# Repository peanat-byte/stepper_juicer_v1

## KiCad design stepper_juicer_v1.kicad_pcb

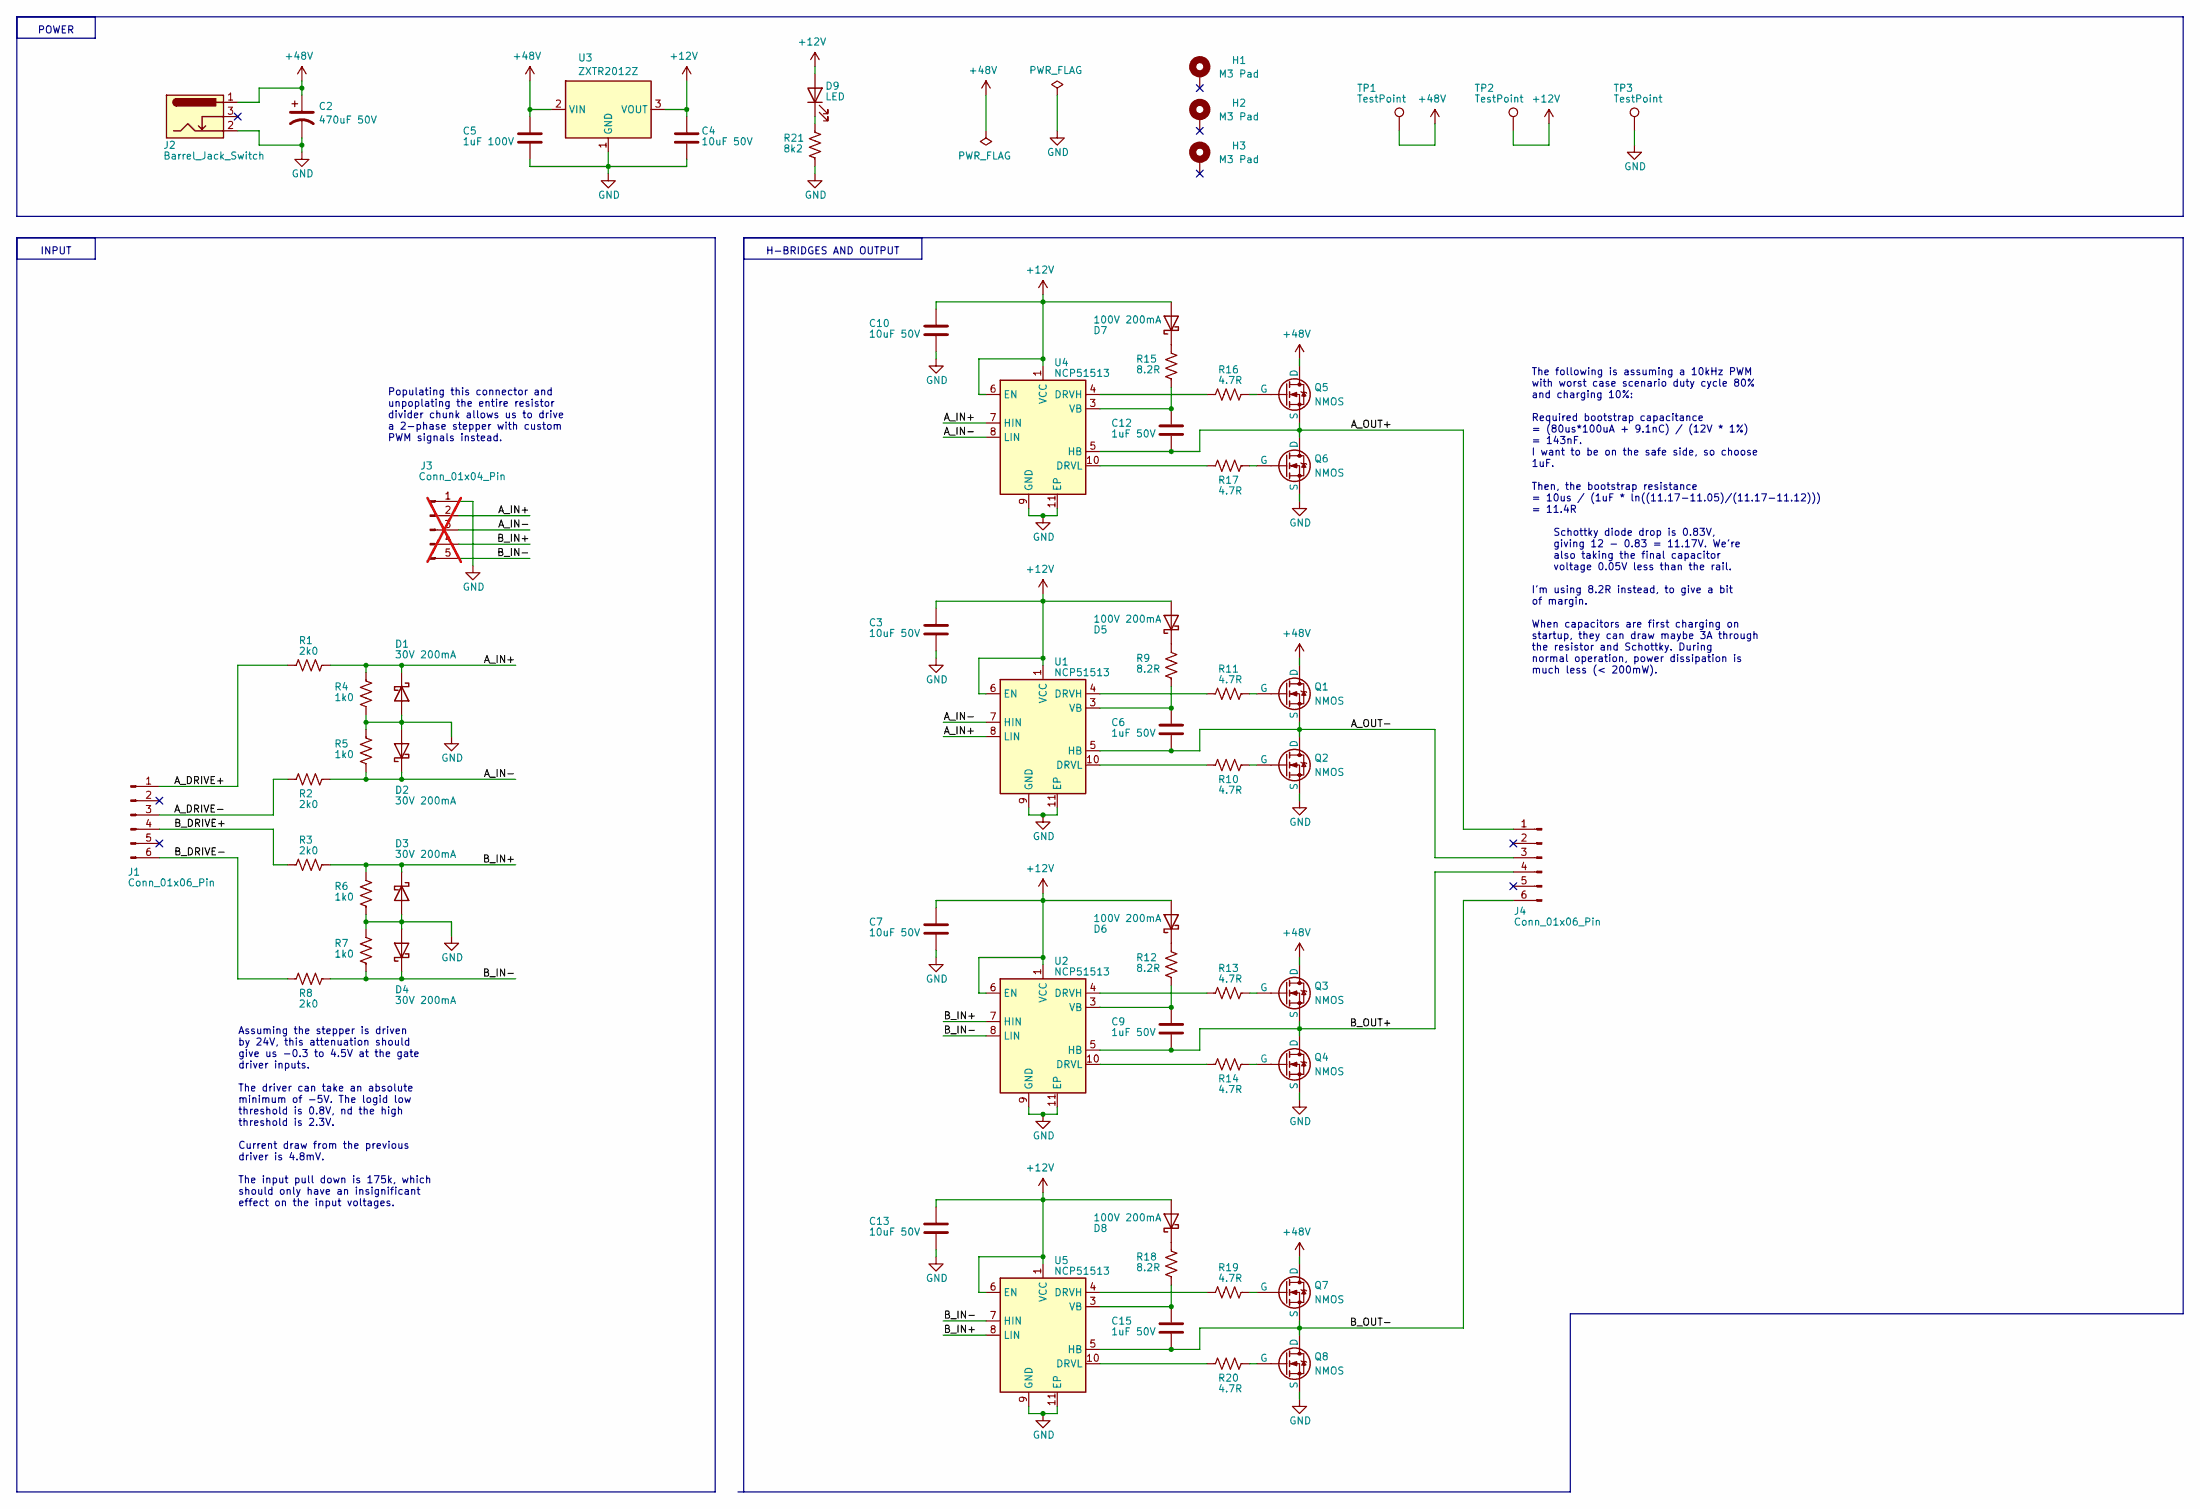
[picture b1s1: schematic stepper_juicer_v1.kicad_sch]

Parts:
C2: 470uF 50V; CP_Radial_D10.0mm_P5.00mm
C3, C4, C7, C10, C13: 10uF 50V; C_0805_2012Metric
C5: 1uF 100V; C_0805_2012Metric
C6, C9, C12, C15: 1uF 50V; C_0805_2012Metric
D1, D2, D3, D4: 30V 200mA; D_SOD-523
D5, D6, D7, D8: 100V 200mA; D_SOD-323F
D9: LED; D_0603_1608Metric
H1, H2, H3: M3 Pad; MountingHole_3.2mm_M3_Pad
J1, J4: Conn_01x06_Pin; JST_PH_B6B-PH-K_1x06_P2.00mm_Vertical
J2: Barrel_Jack_Switch; BarrelJack_GCT_DCJ200-10-A_Horizontal
J3: Conn_01x04_Pin; JST_XH_B5B-XH-A_1x05_P2.50mm_Vertical; not fitted
Q1, Q2, Q3, Q4, Q5, Q6, Q7, Q8: NMOS; PG-TSDSON-8_3.8x2.29_Pitch0.65mm
R1, R2, R3, R8: 2k0; R_0603_1608Metric
R4, R5, R6, R7: 1k0; R_0603_1608Metric
R9, R12, R15, R18: 8.2R; R_0603_1608Metric
R10, R11, R13, R14, R16, R17, R19, R20: 4.7R; R_0805_2012Metric
R21: 8k2; R_0603_1608Metric
TP1, TP2, TP3: TestPoint; TestPoint_Pad_D1.0mm
U1, U2, U4, U5: NCP51513; DFN-10-1EP_3x3mm_P0.5mm_EP1.7x2.5mm
U3: ZXTR2012Z; SOT-89-3

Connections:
+12V: C3.1, C4.1, C7.1, C10.1, C13.1, D5.2 (A), D6.2 (A), D7.2 (A), D8.2 (A), D9.2 (A), TP2.1, U1.1 (VCC), U1.6 (EN), U2.1 (VCC), U2.6 (EN), U3.3 (VOUT), U4.1 (VCC), U4.6 (EN), U5.1 (VCC), U5.6 (EN)
+48V: C2.1, C5.1, J2.1, Q1.1 (D), Q3.1 (D), Q5.1 (D), Q7.1 (D), TP1.1, U3.2 (VIN)
/A_DRIVE+: J1.1, R1.2
/A_DRIVE-: J1.3, R2.2
/A_IN+: D1.1 (K), J3.2, R1.1, R4.1, U1.8 (LIN), U4.7 (HIN)
/A_IN-: D2.1 (K), J3.3, R2.1, R5.2, U1.7 (HIN), U4.8 (LIN)
/A_OUT+: C12.2, J4.1, Q5.3 (S), Q6.1 (D), U4.5 (HB)
/A_OUT-: C6.2, J4.3, Q1.3 (S), Q2.1 (D), U1.5 (HB)
/B_DRIVE+: J1.4, R3.2
/B_DRIVE-: J1.6, R8.2
/B_IN+: D3.1 (K), J3.4, R3.1, R6.1, U2.7 (HIN), U5.8 (LIN)
/B_IN-: D4.1 (K), J3.5, R7.2, R8.1, U2.8 (LIN), U5.7 (HIN)
/B_OUT+: C9.2, J4.4, Q3.3 (S), Q4.1 (D), U2.5 (HB)
/B_OUT-: C15.2, J4.6, Q7.3 (S), Q8.1 (D), U5.5 (HB)
GND: C2.2, C3.2, C4.2, C5.2, C7.2, C10.2, C13.2, D1.2 (A), D2.2 (A), D3.2 (A), D4.2 (A), J2.2, J3.1, Q2.3 (S), Q4.3 (S), Q6.3 (S), Q8.3 (S), R4.2, R5.1, R6.2, R7.1, R21.2, TP3.1, U1.9 (GND), U1.11 (EP), U2.9 (GND), U2.11 (EP), U3.1 (GND), U4.9 (GND), U4.11 (EP), U5.9 (GND), U5.11 (EP)
unnamed: D5.1 (K), R9.2
unnamed: D6.1 (K), R12.2
unnamed: D7.1 (K), R15.2
unnamed: D8.1 (K), R18.2
unnamed: D9.1 (K), R21.1
unnamed: Q1.2 (G), R11.1
unnamed: Q2.2 (G), R10.1
unnamed: Q3.2 (G), R13.1
unnamed: Q4.2 (G), R14.1
unnamed: Q5.2 (G), R16.1
unnamed: Q6.2 (G), R17.1
unnamed: Q7.2 (G), R19.1
unnamed: Q8.2 (G), R20.1
unnamed: R11.2, U1.4 (DRVH)
unnamed: R10.2, U1.10 (DRVL)
unnamed: C6.1, R9.1, U1.3 (VB)
unnamed: R13.2, U2.4 (DRVH)
unnamed: R14.2, U2.10 (DRVL)
unnamed: C9.1, R12.1, U2.3 (VB)
unnamed: R16.2, U4.4 (DRVH)
unnamed: R17.2, U4.10 (DRVL)
unnamed: C12.1, R15.1, U4.3 (VB)
unnamed: R19.2, U5.4 (DRVH)
unnamed: R20.2, U5.10 (DRVL)
unnamed: C15.1, R18.1, U5.3 (VB)

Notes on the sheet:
H-BRIDGES AND OUTPUT
The following is assuming a 10kHz PWM with worst case scenario duty cycle 80% and charging 10%: Required bootstrap capacitance = (80us*100uA + 9.1nC) / (12V * 1%) = 143nF. I want to be on the safe side, so choose 1uF. Then, the bootstrap resistance = 10us / (1uF * ln((11.17-11.05)/(11.17-11.12))) =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
INPUT
Assuming the stepper is driven by 24V, this attenuation should give us -0.3 to 4.5V at the gate driver inputs. The driver can take an absolute minimum of -5V. The logid low threshold is 0.8V, nd the high threshold is 2.3V. Current draw from the previous driver is 4.8mV. The input pull down is 175k,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
POWER
Populating this connector and unpoplating the entire resistor divider chunk allows us to drive a 2-phase stepper with custom PWM signals instead.

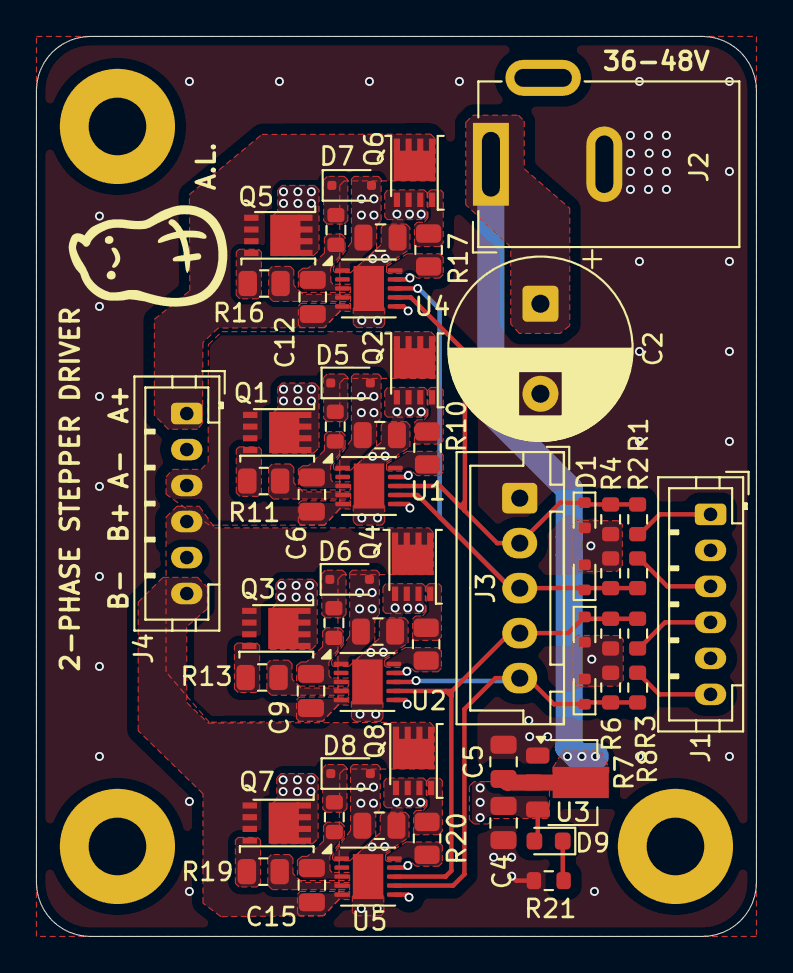
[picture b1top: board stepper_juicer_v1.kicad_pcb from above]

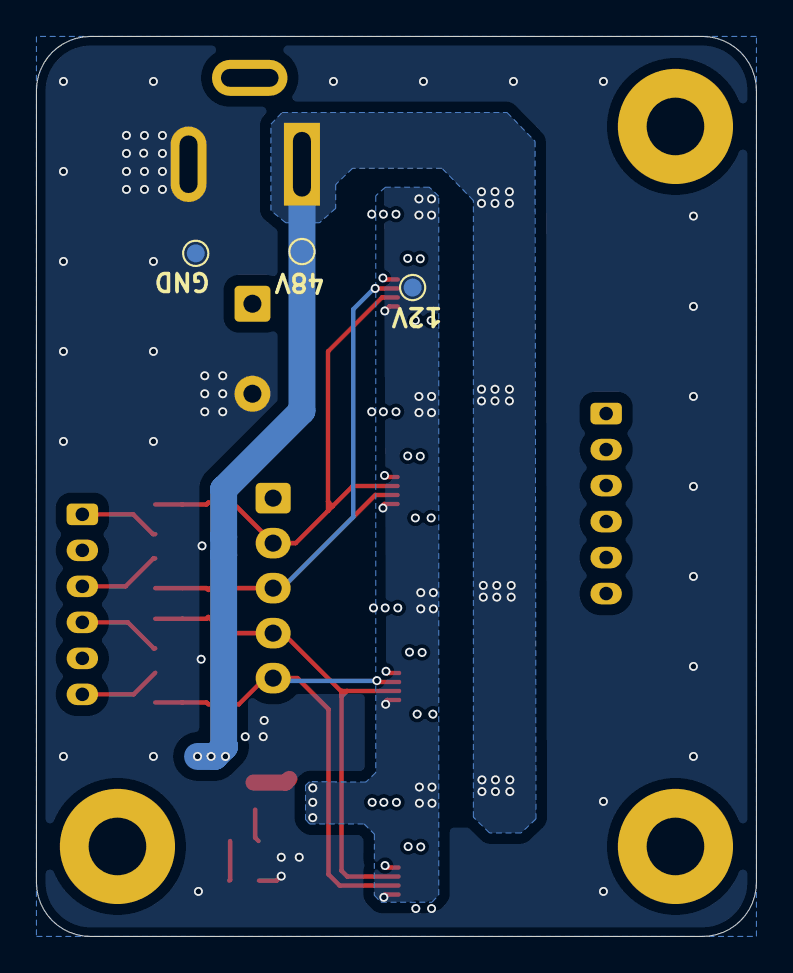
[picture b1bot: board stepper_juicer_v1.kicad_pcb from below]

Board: 4 copper layers, 40.0 x 50.0 mm, 64 parts (3 on the bottom side), 40 nets.

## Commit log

2025-09-14 Start schematic
2025-09-15 Schematic done
2025-09-22 Finish design
2025-09-26 Add ground pin
2025-09-26 fixup! Add ground pin
    Cosmetic change
